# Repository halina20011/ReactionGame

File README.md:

# Reaction Game

### Images

## Datasheet
ATtiny24A: <a href="https://ww1.microchip.com/downloads/en/DeviceDoc/ATtiny24A-44A-84A-DataSheet-DS40002269A.pdf">ATtiny24A-44A-84A-DataSheet.pdf</a>

## Removing 8 clock prescaler
`avrdude -p t24a -c avrisp -P /dev/ttyUSB0 -b 19200 -U lfuse:w:0b11100010:m`

## Current
Voltage 3V
led voltage drop = 1V 
V = IR
I = V/R
I = 2/220
I = 0.009A
I = 9mA

## Flash
I am using Arduino Uno as ISP (in system programmer) </br>
To flash code to the board connect Arduino Uno and the 6 pin header (from left top going clockwise)
Arduino Uno | 6 pin header
----------- | ------------
13          | SCK
10          | Reset
11          | MOSI
5V          | VCC
GND         | GND
12          | MISO

`make flash`

## Components
Name                            | Net   | Cost
------------------------------- | ----- | ----
Attiny24A-U                     | 1x    | x
12mm push button                | 1x    | x
74HC595                         | 1x    | x
7 segments 4 digits SH5461AS    | 1x    | x
1206 220Ohm SMD resistor        | 7x    | x
Switch SS12F47                  | 1x    | x
Battery holder                  | 1x    | x
=                               |       | 
Total                           | 13    | x

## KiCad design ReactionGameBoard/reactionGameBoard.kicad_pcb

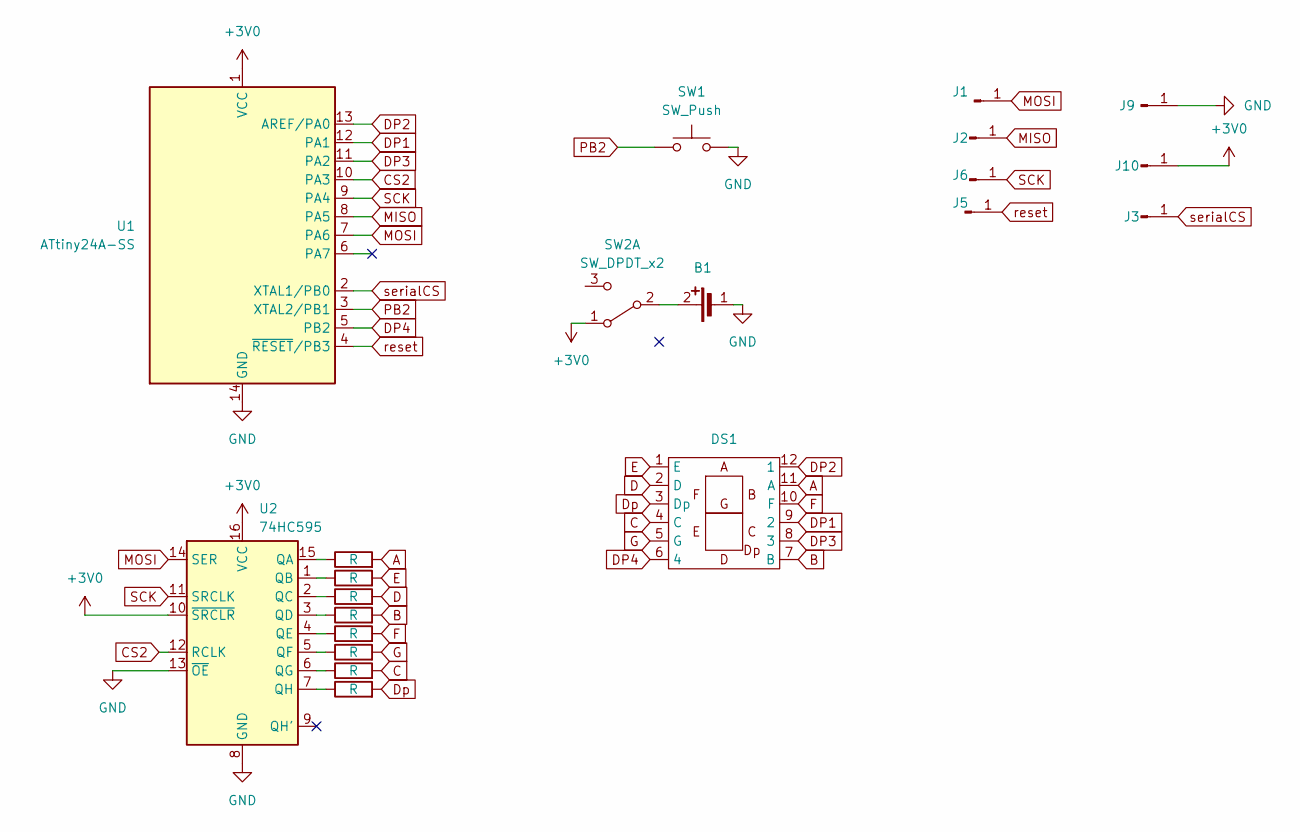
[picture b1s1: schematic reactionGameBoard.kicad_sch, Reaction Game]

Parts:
B1: DS1092
DS1: SH5461AS
J1, J2, J3, J5, J6, J9, J10: Conn_01x01_Pin; PinHeader_1x01_P2.54mm_Vertical
R1, R2, R3, R4, R5, R6, R7, R8: R; R_1206_3216Metric
SW1: SW_Push; SW_PUSH-12mm
SW2: SW_DPDT_x2; SS12F47
U1: ATtiny24A-SS; SOIC-14_3.9x8.7mm_P1.27mm
U2: 74HC595; DIP-16_W7.62mm

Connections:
+3V0: J10.1, SW2.1 (A), U1.1 (VCC), U2.10 (~SRCLR), U2.16 (VCC)
A: DS1.11 (A), R1.2
B: DS1.7 (B), R4.2
C: DS1.4 (C), R7.2
CS2: U1.10 (PA3), U2.12 (RCLK)
D: DS1.2 (D), R3.2
DP1: DS1.9 (2), U1.12 (PA1)
DP2: DS1.12 (1), U1.13 (AREF/PA0)
DP3: DS1.8 (3), U1.11 (PA2)
DP4: DS1.6 (4), U1.5 (PB2)
Dp: DS1.3 (Dp), R8.2
E: DS1.1 (E), R2.2
F: DS1.10 (F), R5.2
G: DS1.5 (G), R6.2
GND: B1.1, J9.1, SW1.2, U1.14 (GND), U2.8 (GND), U2.13 (~OE)
MISO: J2.1, U1.8 (PA5)
MOSI: J1.1, U1.7 (PA6), U2.14 (SER)
unnamed: B1.2, SW2.2 (B)
unnamed: R1.1, U2.15 (QA)
unnamed: R2.1, U2.1 (QB)
unnamed: R3.1, U2.2 (QC)
unnamed: R4.1, U2.3 (QD)
unnamed: R5.1, U2.4 (QE)
unnamed: R6.1, U2.5 (QF)
unnamed: R7.1, U2.6 (QG)
unnamed: R8.1, U2.7 (QH)
PB2: SW1.1, U1.3 (XTAL2/PB1)
SCK: J6.1, U1.9 (PA4), U2.11 (SRCLK)
reset: J5.1, U1.4 (~RESET/PB3)
serialCS: J3.1, U1.2 (XTAL1/PB0)

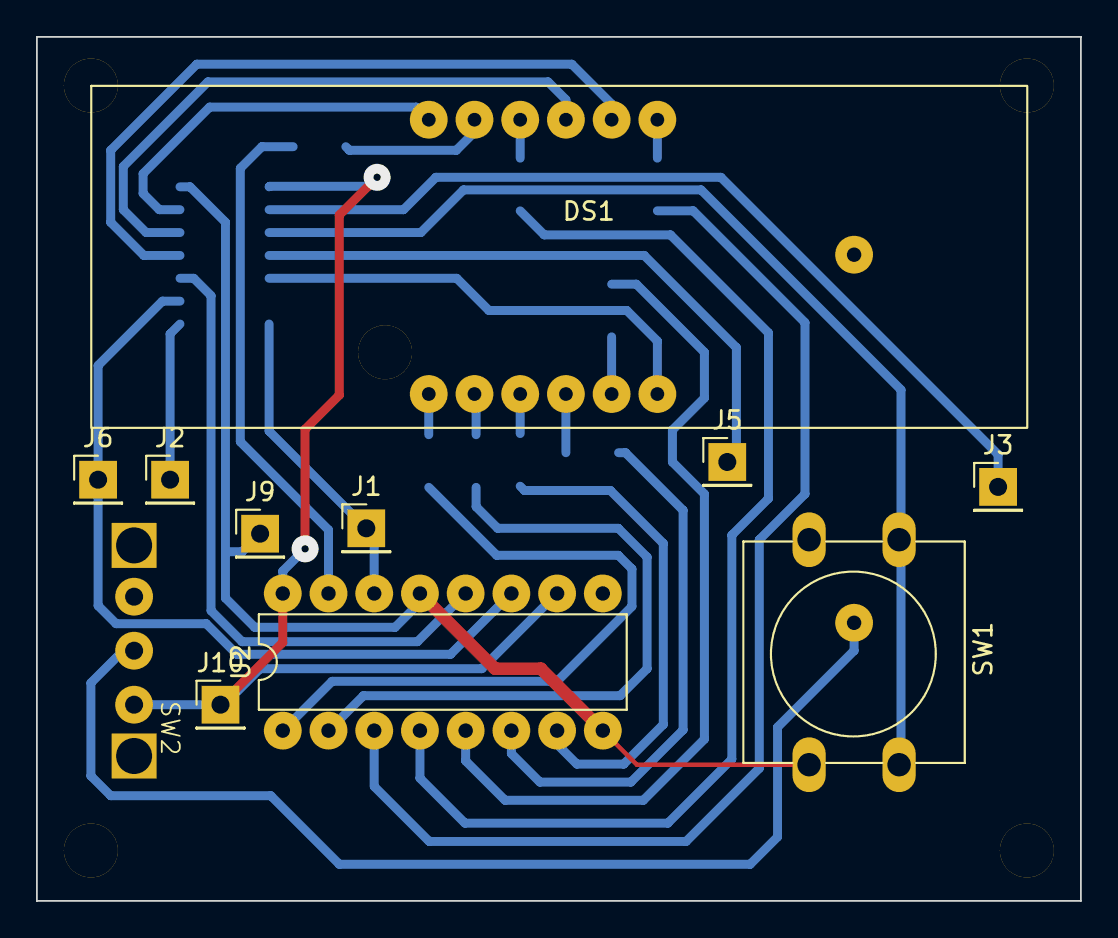
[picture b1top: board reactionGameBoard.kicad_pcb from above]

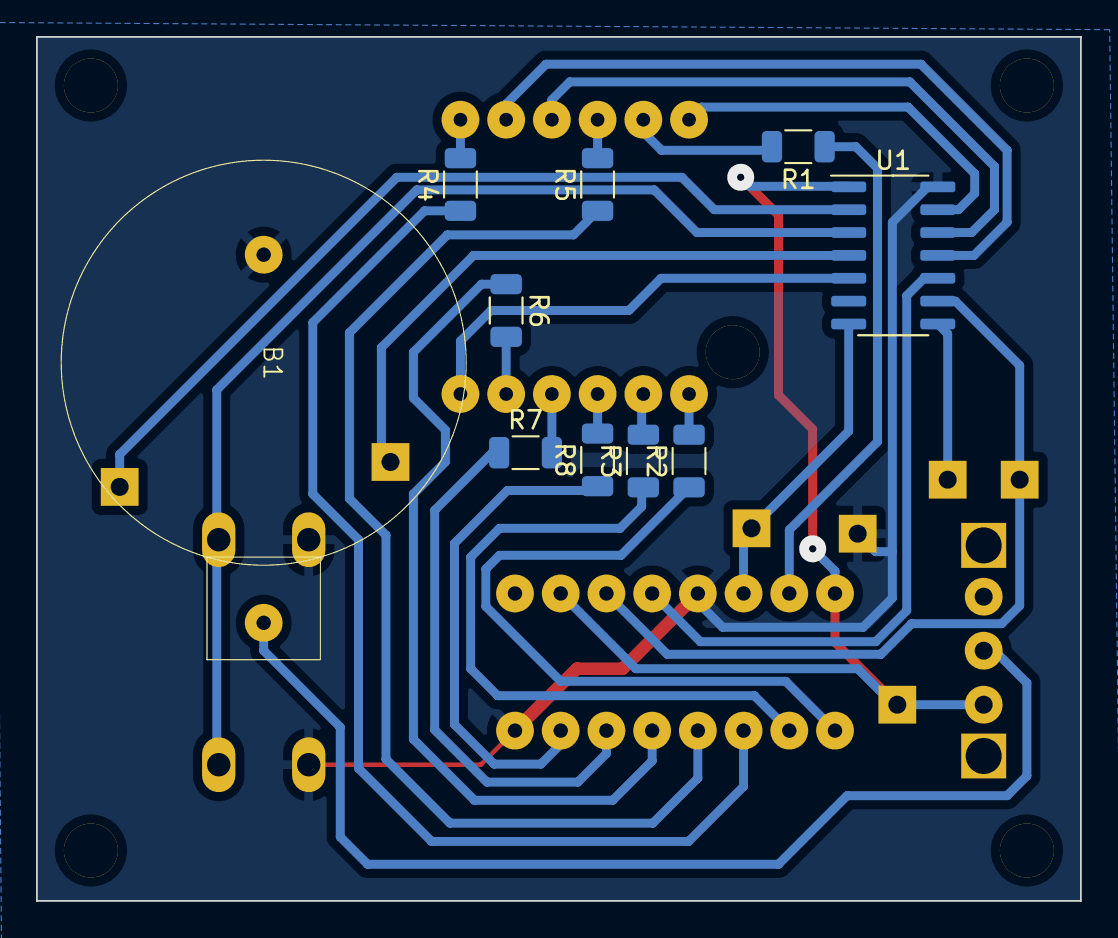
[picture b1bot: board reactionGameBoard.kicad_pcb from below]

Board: 2 copper layers, 58.0 x 48.0 mm, 26 parts (10 on the bottom side), 30 nets.

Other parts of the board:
H**: hole-3.0mm
H**#2, H**#3, H**#4, H**#5: hole-3.0mm

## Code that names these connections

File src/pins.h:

#ifndef PINS
#define PINS

#include <avr/io.h>

#define SPI_DDR     DDRA
#define SPI_PORT    PORTA
#define SCK         PA4
#define MISO        PA5
#define MOSI        PA6

#define CSS_DDR     DDRB
#define CSS_PORT    PORTB
#define CSS         PB0
#define CSD_DDR     DDRA
#define CSD_PORT    PORTA
#define CSD         PA3

// TODO: move DP3 to PA7
// display pins
#define DP1_DDR     DDRA
#define DP1_PORT    PORTA
#define DP1         PA1

#define DP2_DDR     DDRA
#define DP2_PORT    PORTA
#define DP2         PA0

#define DP3_DDR     DDRB
#define DP3_PORT    PORTB
#define DP3         PB2

#define DP4_DDR     DDRA
#define DP4_PORT    PORTA
#define DP4         PA2

#define BUTTON_DDR  DDRA
#define BUTTON_PORT PORTA
#define BUTTON_PIN  PINA
#define BUTTON      PA0

#endif 

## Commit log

2023-12-23 beginning
2024-07-19 new board design + code
2024-10-02 cnc pcb version
